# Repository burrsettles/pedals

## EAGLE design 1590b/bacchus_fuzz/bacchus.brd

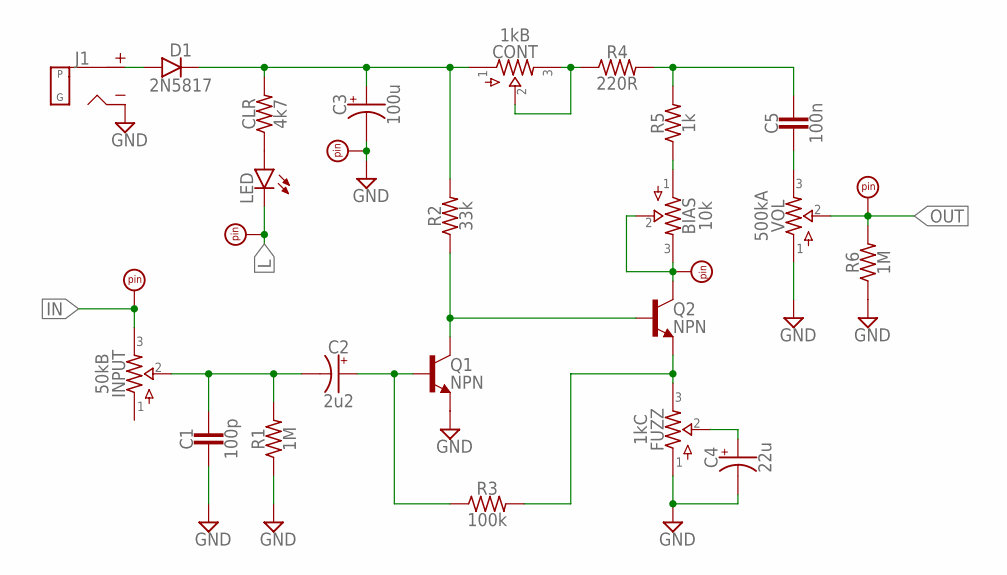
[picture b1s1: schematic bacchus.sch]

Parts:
BIAS: 10k; 2262_TRIM
C1: 100p; 050X030_025_2
C2: 2u2; 050_020_1
C3: 100u; 050_020_1
C4: 22u; 050_020_1
C5: 100n; 050X030_025_2
CLR: 4k7; R0207/3
CONT: 1kB; 9MM_W/MOUNTS
D1: 2N5817; DO41-3
FUZZ: 1kC; 9MM_W/MOUNTS
GND: PADRND; ROUND
IN: PADSQR; SQUARE
INPUT: 50kB; 9MM_W/MOUNTS
J1: DC_MONO; DC
L: PADRND; ROUND
LED: LEDB; 3MM_B
OUT: PADSQR; SQUARE
Q1, Q2: NPN; TO5
R1, R6: 1M; R0207/3
R2: 33k; R0207/3
R3: 100k; R0207/3
R4: 220R; R0207/3
R5: 1k; R0207/3
TP: PADSQR; SQUARE
VOL: 500kA; 9MM_W/MOUNTS

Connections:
GND: C1.2, C3.-, C4.-, FUZZ.P$1 (1), GND.1, J1.S (SLEEVE), Q1.1 (E), R1.1, R6.1, VOL.P$1 (1)
IN: IN.1, INPUT.P$3 (3)
L: L.1, LED.K (C)
unnamed: C1.1, C2.-, INPUT.P$2 (2), R1.2
unnamed: C2.+, Q1.2 (B), R3.1
unnamed: Q1.3 (C), Q2.2 (B), R2.1
unnamed: D1.A, J1.T (TIP)
unnamed: C3.+, CLR.2, CONT.P$1 (1), D1.C, R2.2
unnamed: CONT.P$2 (2), CONT.P$3 (3), R4.1
unnamed: CLR.1, LED.A
unnamed: C5.1, R4.2, R5.2
unnamed: BIAS.1, R5.1
unnamed: BIAS.2, BIAS.3, Q2.3 (C), TP.1
unnamed: C5.2, VOL.P$3 (3)
unnamed: FUZZ.P$3 (3), Q2.1 (E), R3.2
unnamed: C4.+, FUZZ.P$2 (2)
OUT: OUT.1, R6.2, VOL.P$2 (2)

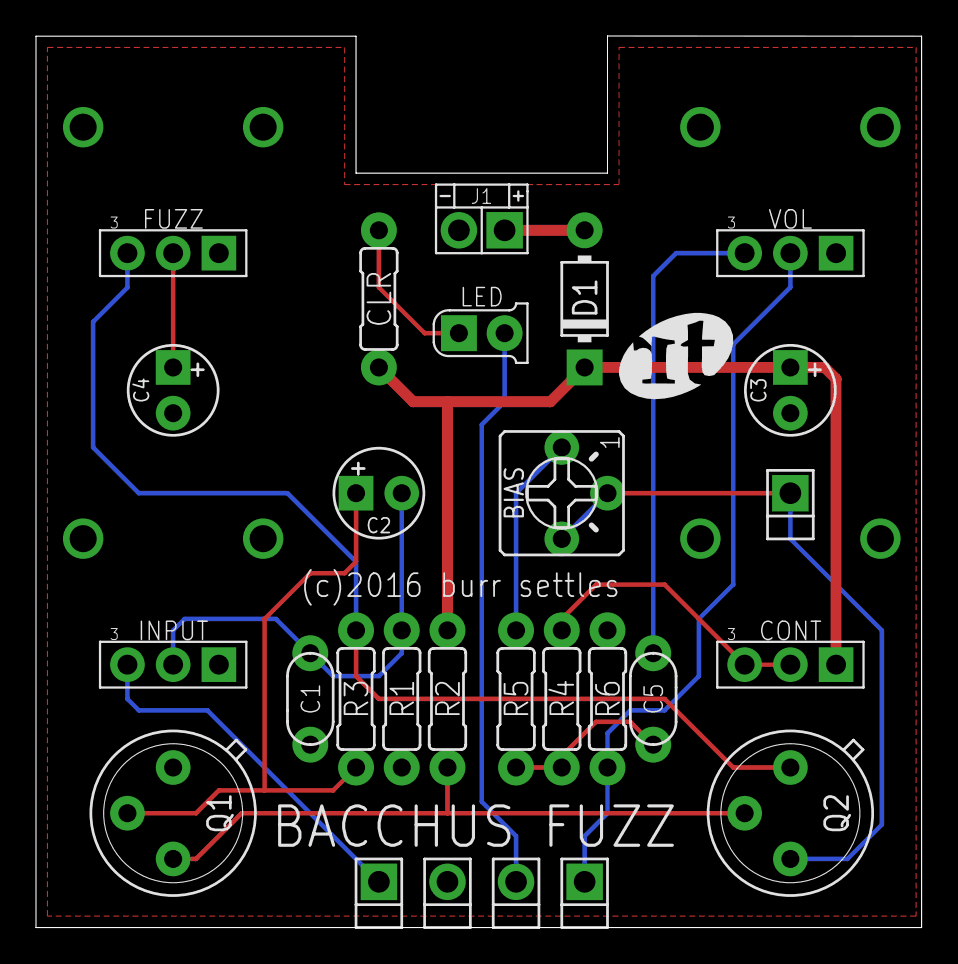
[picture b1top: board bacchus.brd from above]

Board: 2 copper layers, 49.2 x 49.5 mm, 28 parts (0 on the bottom side), 17 nets.

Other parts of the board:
U$4: RT0250

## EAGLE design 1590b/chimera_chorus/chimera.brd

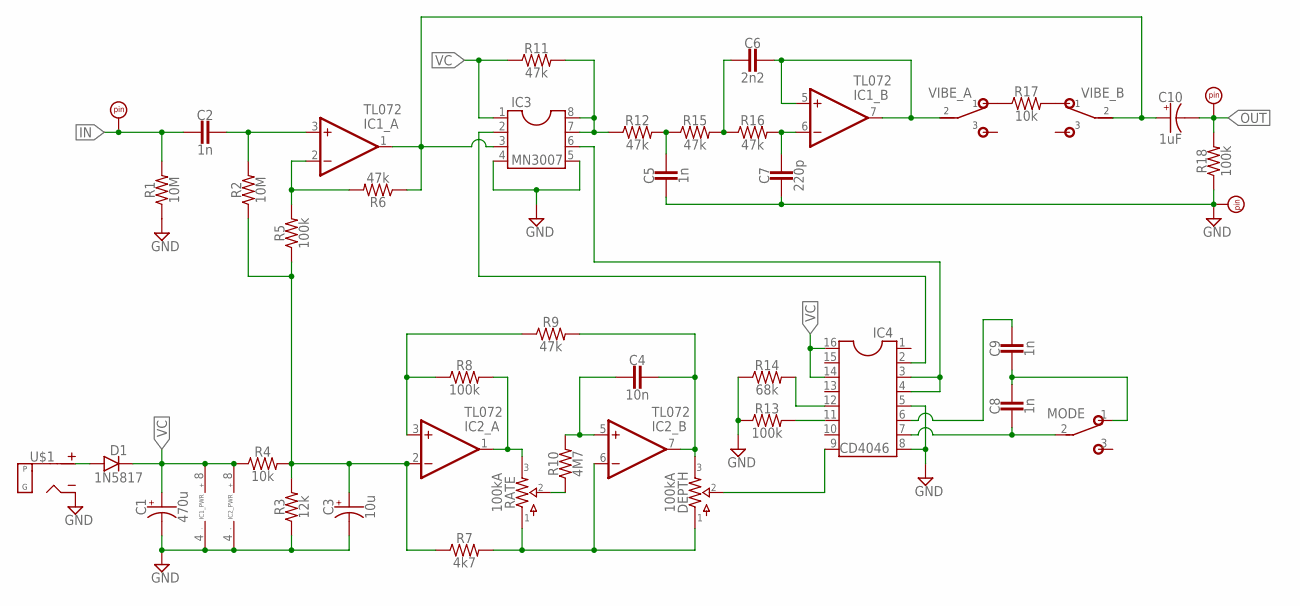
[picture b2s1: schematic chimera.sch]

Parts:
C1: 470u; 080_035
C2, C5, C8, C9: 1n; 050X030_025_2
C3: 10u; 050_020_1
C4: 10n; BOX_MED
C6: 2n2; 050X030_025_2
C7: 220p; 050X030_025_2
C10: 1uF; 080_035
D1: 1N5817; DO41-2
DEPTH: 100kA; 16MM
GND: PADRND; ROUND
IC1, IC2: TL072; DIL08
IC3: MN3007; DIL08
IC4: CD4046; DIL16
IN: PADSQR; SQUARE
MODE: SPDTPIN_MOUNT; 1MS1T1B1C0M2QE
OUT: PADSQR; SQUARE
R1, R2: 10M; R0207/3
R3: 12k; R0207/3
R4, R17: 10k; R0207/3
R5, R8, R13, R18: 100k; R0207/3
R6, R9, R11, R12, R15, R16: 47k; R0207/3
R7: 4k7; R0207/3
R10: 4M7; R0207/3
R14: 68k; R0207/3
RATE: 100kA; 16MM
U$1: DC_MONO; DC
VIBE: DPDTTAIWAY1MD; TAIWAY1MD

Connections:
GND: C1.-, C3.-, C5.1, C7.2, GND.1, IC1.4 (V-), IC2.4 (V-), IC3.4, IC3.5, IC4.5, IC4.8, R1.1, R3.1, R13.1, R14.1, R18.1, U$1.S (SLEEVE)
IN: C2.1, IN.1, R1.2
unnamed: C2.2, IC1.3 (+IN), R2.2
unnamed: IC1.2 (-IN), R5.2, R6.2
unnamed: C10.+, IC1.1 (OUT), IC3.3, R6.1, VIBE.B2 (2)
unnamed: DEPTH.1, IC2.6 (-IN), R7.2, RATE.1
unnamed: C4.2, IC2.5 (+IN), R10.2
unnamed: R17.1, VIBE.A1 (1)
unnamed: IC2.3 (+IN), R8.1, R9.1
unnamed: IC2.1 (OUT), R8.2, RATE.3
unnamed: DEPTH.2, IC4.9
unnamed: C4.1, DEPTH.3, IC2.7 (OUT), R9.2
unnamed: R10.1, RATE.2
unnamed: IC4.11, R13.2
unnamed: IC4.12, R14.2
unnamed: C8.1, IC4.7, MODE.2
unnamed: IC3.2, IC4.2
unnamed: IC3.7, IC3.8, R11.2, R12.1
unnamed: C7.1, IC1.6 (-IN), R16.2
unnamed: C5.2, R12.2, R15.1
unnamed: C6.2, R15.2, R16.1
unnamed: C6.1, IC1.5 (+IN), IC1.7 (OUT), VIBE.A2 (2)
unnamed: C9.2, IC4.6
unnamed: IC3.6, IC4.3, IC4.4
unnamed: R17.2, VIBE.B1 (1)
unnamed: C8.2, C9.1, MODE.1 (O)
unnamed: C3.+, IC2.2 (-IN), R2.1, R3.2, R4.2, R5.1, R7.1
unnamed: D1.A, U$1.T (TIP)
OUT: C10.-, OUT.1, R18.2
VC: C1.+, D1.C, IC1.8 (V+), IC2.8 (V+), IC3.1, IC4.14, IC4.16, R4.1, R11.1

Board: 2 copper layers, 41 parts (0 on the bottom side), 30 nets, no tracks yet.

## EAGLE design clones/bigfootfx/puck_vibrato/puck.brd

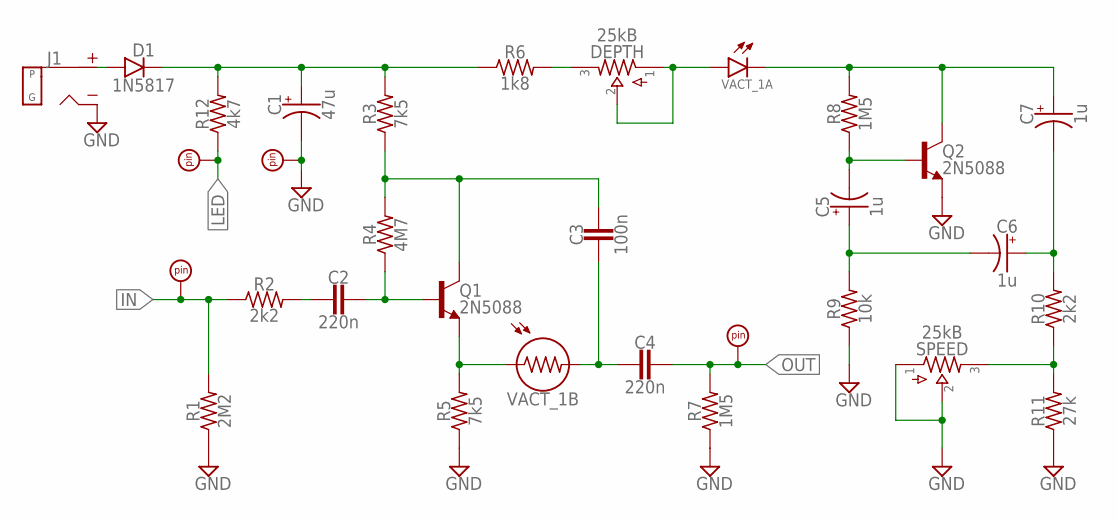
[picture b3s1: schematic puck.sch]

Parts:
C1: 47u; 050_020_1
C2, C4: 220n; 050X030_025_2
C3: 100n; 050X030_025_2
C5, C6, C7: 1u; 050_020
D1: 1N5817; DO41-3
DEPTH: 25kB; 2262_TRIM
GND: PADRND; ROUND
IN: PADSQR; SQUARE
J1: DC_MONO; DC
LED: PADRND; ROUND
OUT: PADSQR; SQUARE
Q1, Q2: 2N5088; TO92-
R1: 2M2; R0207/3
R2, R10: 2k2; R0207/3
R3, R5: 7k5; R0207/3
R4: 4M7; R0207/3
R6: 1k8; R0207/3
R7, R8: 1M5; R0207/3
R9: 10k; R0207/3
R11: 27k; R0207/3
R12: 4k7; R0207/3
SPEED: 25kB; PADS_SMALL
VACT_1: VACTROL; _LDR

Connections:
GND: C1.-, GND.1, J1.S (SLEEVE), Q2.3 (E), R1.1, R5.1, R7.1, R9.1, R11.1, SPEED.1, SPEED.2
IN: IN.1, R1.2, R2.1
LED: LED.1, R12.1
unnamed: D1.A, J1.T (TIP)
unnamed: C1.+, D1.C, R3.2, R6.1, R12.2
unnamed: C3.1, Q1.1 (C), R3.1, R4.2
unnamed: C2.1, Q1.2 (B), R4.1
unnamed: C7.+, Q2.1 (C), R8.2, VACT_1.CATHODE
unnamed: C2.2, R2.2
unnamed: DEPTH.3, R6.2
unnamed: DEPTH.1, DEPTH.2, VACT_1.ANODE
unnamed: C5.-, Q2.2 (B), R8.1
unnamed: Q1.3 (E), R5.2, VACT_1.1
unnamed: C3.2, C4.2, VACT_1.2
unnamed: C6.+, C7.-, R10.2
unnamed: C5.+, C6.-, R9.2
unnamed: R10.1, R11.2, SPEED.3
OUT: C4.1, OUT.1, R7.2

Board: 2 copper layers, 30 parts (1 on the bottom side), 18 nets, no tracks yet.

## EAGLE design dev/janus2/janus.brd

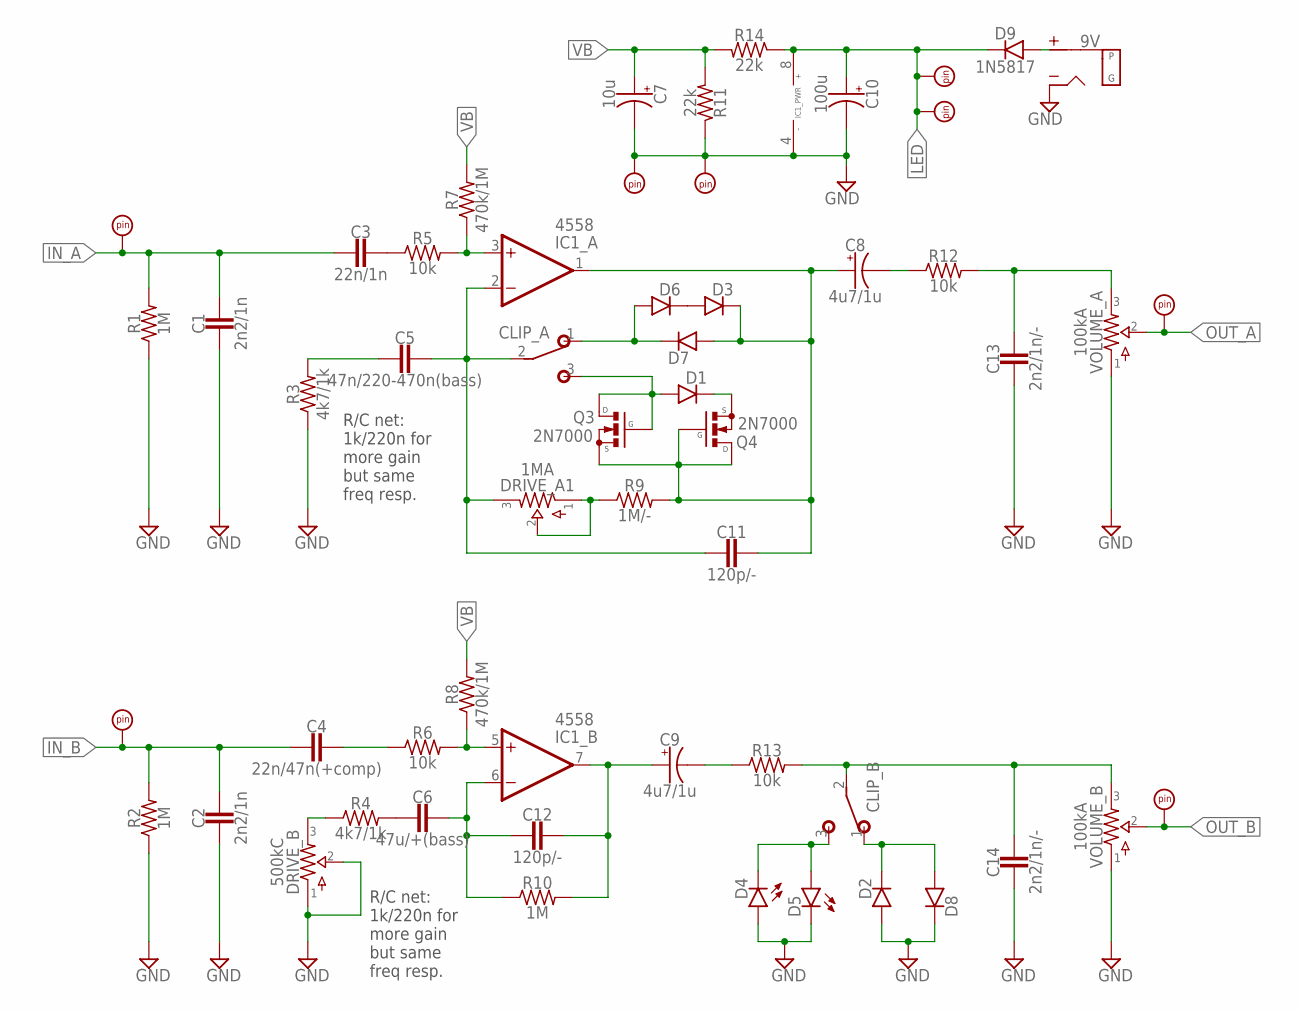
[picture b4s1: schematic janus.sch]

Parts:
9V: DC_MONO; DC
C1, C2: 2n2/1n; 050X030_025_2
C3: 22n/1n; 050X030_025_2
C4: 22n/47n(+comp); 050X030_025_2
C5: 47n/220-470n(bass); 050X030_025_2
C6: 47u/+(bass); 050X030_025_2
C7: 10u; 050_020_1
C8, C9: 4u7/1u; 050_020_1
C10: 100u; 050_020_1
C11, C12: 120p/-; 050X030_025_2
C13, C14: 2n2/1n/-; 050X030_025_2
CLIP_A: SPDTPADS; SPDT
CLIP_B: SPDTPADS; SPDT
D1, D2, D3, D6, D7, D8: DO35.2; DO35-2
D4, D5: LEDB; 3MM_B
D9: 1N5817; DO41-3
DRIVE_A1: 1MA; 16MM
DRIVE_B: 500kC; 16MM
GNDA: PADRND; ROUND
GNDB: PADRND; ROUND
IC1: 4558; DIL08
INA: PADSQR; SQUARE
INB: PADSQR; SQUARE
LEDA: PADRND; ROUND
LEDB: PADRND; ROUND
OUTA: PADSQR; SQUARE
OUTB: PADSQR; SQUARE
Q3, Q4: 2N7000; SOT54ES
R1, R2, R10: 1M; R0207/3
R3, R4: 4k7/1k; R0207/3
R5, R6, R12, R13: 10k; R0207/3
R7, R8: 470k/1M; R0207/3
R9: 1M/-; R0207/3
R11, R14: 22k; R0207/3
VOLUME_A: 100kA; 16MM
VOLUME_B: 100kA; 16MM

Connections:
GND: 9V.S (SLEEVE), C1.2, C2.2, C7.-, C10.-, C13.2, C14.2, D2.A, D4.A, D5.K (C), D8.C, DRIVE_B.1, DRIVE_B.2, GNDA.1, GNDB.1, IC1.4 (V-), R1.1, R2.1, R3.1, R11.1, VOLUME_A.1, VOLUME_B.1
IN_A: C1.1, C3.2, INA.1, R1.2
IN_B: C2.1, C4.2, INB.1, R2.2
LED: C10.+, D9.C, IC1.8 (V+), LEDA.1, LEDB.1, R14.1
unnamed: C3.1, R5.1
unnamed: C5.2, R3.2
unnamed: C8.-, R12.1
unnamed: C4.1, R6.1
unnamed: IC1.3 (+IN), R5.2, R7.1
unnamed: DRIVE_A1.1, DRIVE_A1.2, R9.1
unnamed: C5.1, C11.2, CLIP_A.2, DRIVE_A1.3, IC1.2 (-IN)
unnamed: D1.C, Q4.S
unnamed: C13.1, R12.2, VOLUME_A.3
unnamed: CLIP_B.1 (O), D2.C, D8.A
unnamed: C6.2, R4.2
unnamed: C9.-, R13.1
unnamed: 9V.T (TIP), D9.A
unnamed: C8.+, C11.1, D3.C, D7.A, IC1.1 (OUT), Q3.S, Q4.D, Q4.G, R9.2
unnamed: IC1.5 (+IN), R6.2, R8.1
unnamed: C9.+, C12.1, IC1.7 (OUT), R10.2
unnamed: C6.1, C12.2, IC1.6 (-IN), R10.1
unnamed: CLIP_B.3 (S), D4.K (C), D5.A
unnamed: C14.1, CLIP_B.2, R13.2, VOLUME_B.3
unnamed: DRIVE_B.3, R4.1
unnamed: CLIP_A.3 (S), D1.A, Q3.D, Q3.G
unnamed: D3.A, D6.C
unnamed: CLIP_A.1 (O), D6.A, D7.C
OUT_A: OUTA.1, VOLUME_A.2
OUT_B: OUTB.1, VOLUME_B.2
VB: C7.+, R7.2, R8.2, R11.2, R14.2

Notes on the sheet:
R/C net: 1k/220n for more gain but same freq resp.

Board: 2 copper layers, 67 parts (0 on the bottom side), 30 nets, no tracks yet.

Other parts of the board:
U$1: 1590BB
U$2, U$3: 3PDT
U$4, U$5, U$6, U$7, U$11, U$12: LED
U$8, U$9: MONO_ENCLOSED
U$10: DC_TOP

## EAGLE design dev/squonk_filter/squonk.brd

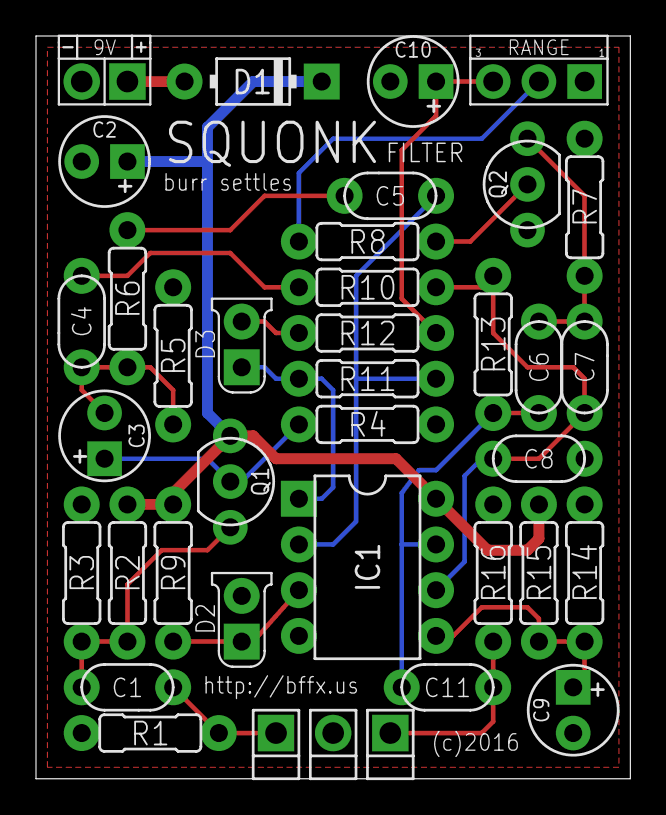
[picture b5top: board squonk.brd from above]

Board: 2 copper layers, 33.0 x 41.3 mm, 39 parts (0 on the bottom side), 21 nets.

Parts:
9V: DC_MONO; DC
C1, C5, C11: 47n; 050X030_025_2
C2: 47u; 050_020_1
C3, C9: 10u; 050_020_1
C4: 10n; 050X030_025_2
C6, C7: 4n7; 050X030_025_2
C8: 1n; 050X030_025_2
C10: 22u; 050_020_1
D1: 1N5817; DO41-3
D2, D3: LEDB; 3MM_B
GND: PADRND; ROUND
IC1: TL072; DIL08
IN: PADSQR; SQUARE
OUT: PADSQR; SQUARE
Q1: MPF102; TO92-
Q2: 2N4123; TO92-
R1, R2, R3: 1M; R0207/3
R4, R9: 10k; R0207/3
R5, R6, R7, R14, R15: 47k; R0207/3
R8: 22k; R0207/3
R10, R13, R16: 470k; R0207/3
R11: 3M3; R0207/3
R12: 100R; R0207/3
RANGE: 25k; PADS_SMALL
U$1: BF0150

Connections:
GND: 9V.S, C2.-, C8.2, C9.-, C10.-, D2.K, GND.1, IC1.4, Q2.3, R1.1, R3.1, R4.1, R5.1, R7.1, R14.1, R16.1, RANGE.1
IN: C1.2, IN.1, R1.2
unnamed: C1.1, Q1.1, R2.1, R3.2
unnamed: C3.+, Q1.2, R4.2
unnamed: C3.-, C4.2, R5.2, R6.1
unnamed: C5.2, R6.2
unnamed: D2.A, IC1.3, R9.2
unnamed: C5.1, IC1.2, R11.1
unnamed: D3.A, IC1.1, R11.2
unnamed: D3.K, R12.1
unnamed: C10.+, R12.2, RANGE.3
unnamed: 9V.T, D1.A
unnamed: C7.1, C8.1, IC1.6, R10.2, R13.1
unnamed: Q2.2, R8.2
unnamed: R8.1, RANGE.2
unnamed: C6.2, C7.2, Q2.1, R7.2
unnamed: C6.1, C11.2, IC1.7, R13.2
unnamed: C4.1, R10.1
unnamed: C9.+, IC1.5, R14.2, R15.1
OUT: C11.1, OUT.1, R16.2
VC: C2.+, D1.C, IC1.8, Q1.3, R2.2, R9.1, R15.2

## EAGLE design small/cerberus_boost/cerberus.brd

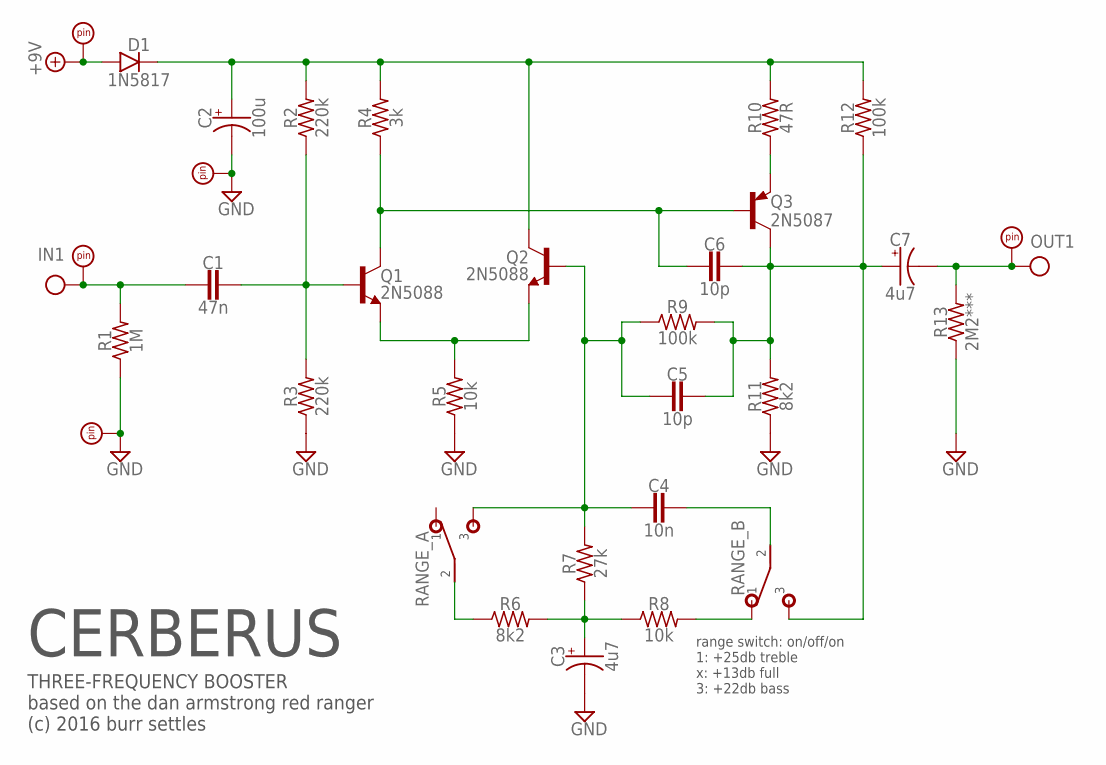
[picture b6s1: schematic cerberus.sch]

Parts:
C1: 47n; BOX_SMALL
C2: 100u; 050_020_1
C3, C7: 4u7; 050_020_1
C4: 10n; BOX_SMALL
C5, C6: 10p; 050X030_025_2
D1: 1N5817; DO41-2
PAD1, PAD2, PAD5: PADSQR; SQUARE
PAD3, PAD4: PADRND; ROUND
Q1, Q2: 2N5088; TO92-
Q3: 2N5087; TO92-
R1: 1M; R0207/3
R2, R3: 220k; R0207/3
R4: 3k; R0207/3
R5, R8: 10k; R0207/3
R6, R11: 8k2; R0207/3
R7: 27k; R0207/3
R9, R12: 100k; R0207/3
R10: 47R; R0207/3
R13: 2M2***; R0207/3
RANGE: DPDT; DPDT_PADS

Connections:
+9V: D1.A, PAD1.1
GND: C2.-, C3.-, PAD3.1, PAD4.1, R1.1, R3.1, R5.1, R11.1, R13.1
IN: C1.2, PAD2.1, R1.2
unnamed: C1.1, Q1.2 (B), R2.1, R3.2
unnamed: Q3.3 (E), R10.1
unnamed: C6.2, Q1.1 (C), Q3.2 (B), R4.1
unnamed: Q1.3 (E), Q2.3 (E), R5.2
unnamed: C5.1, C6.1, C7.+, Q3.1 (C), R9.2, R11.2, R12.1, RANGE.P$6 (3)
unnamed: C2.+, D1.C, Q2.1 (C), R2.2, R4.2, R10.2, R12.2
unnamed: R6.1, RANGE.P$2 (2)
unnamed: C4.1, RANGE.P$5 (2)
unnamed: C4.2, C5.2, Q2.2 (B), R7.2, R9.1, RANGE.P$3 (3)
unnamed: C3.+, R6.2, R7.1, R8.1
unnamed: R8.2, RANGE.P$4 (1)
OUT: C7.-, PAD5.1, R13.2

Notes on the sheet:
CERBERUS
THREE-FREQUENCY BOOSTER based on the dan armstrong red ranger (c) 2016 burr settles
range switch: on/off/on 1: +25db treble x: +13db full 3: +22db bass

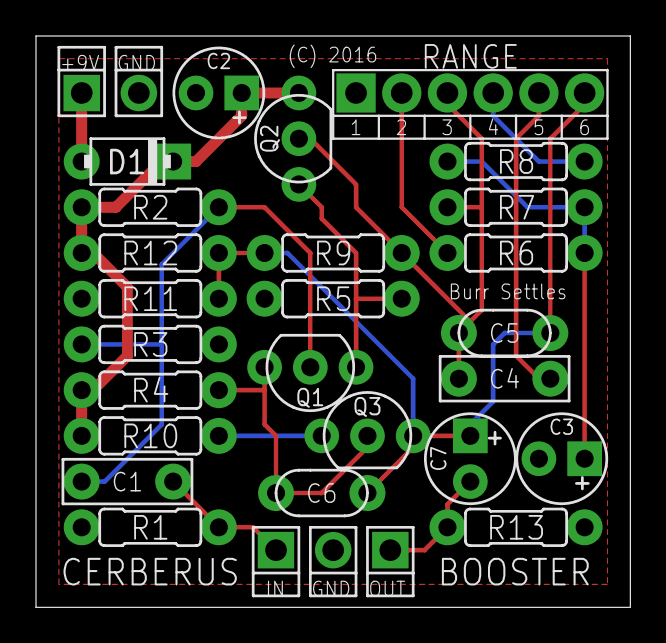
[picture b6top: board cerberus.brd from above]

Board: 2 copper layers, 33.0 x 31.7 mm, 30 parts (0 on the bottom side), 15 nets.

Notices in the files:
small/janus_drive/janus.sch:
© 2016 burr settles
